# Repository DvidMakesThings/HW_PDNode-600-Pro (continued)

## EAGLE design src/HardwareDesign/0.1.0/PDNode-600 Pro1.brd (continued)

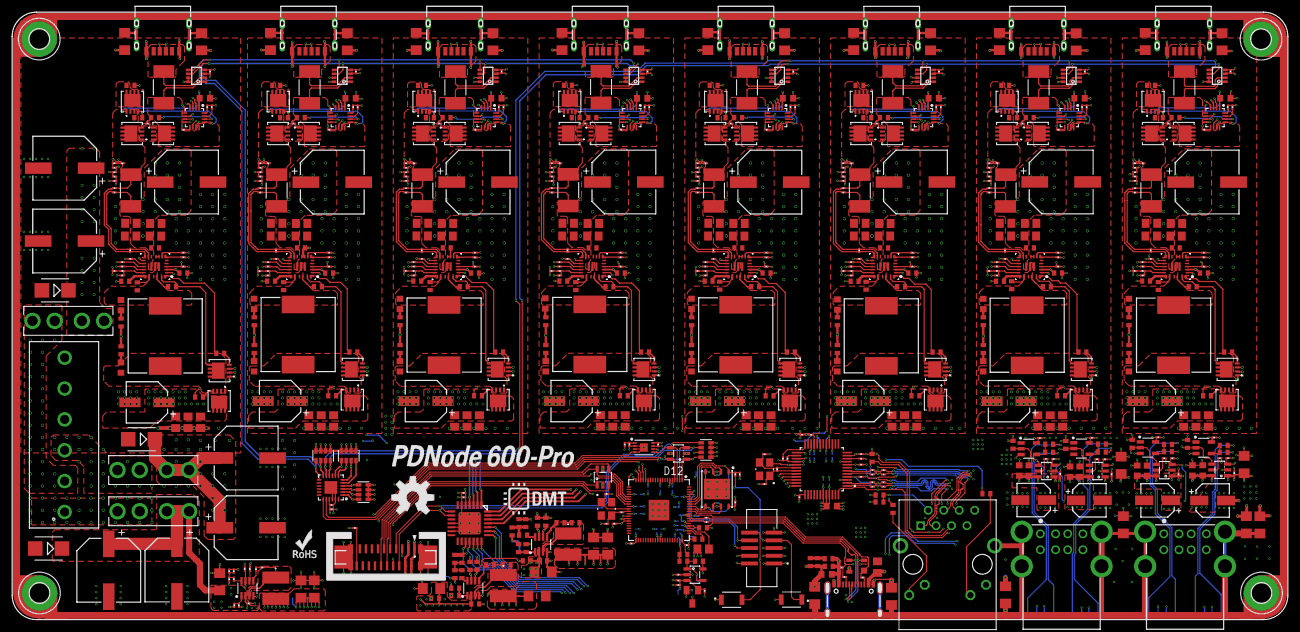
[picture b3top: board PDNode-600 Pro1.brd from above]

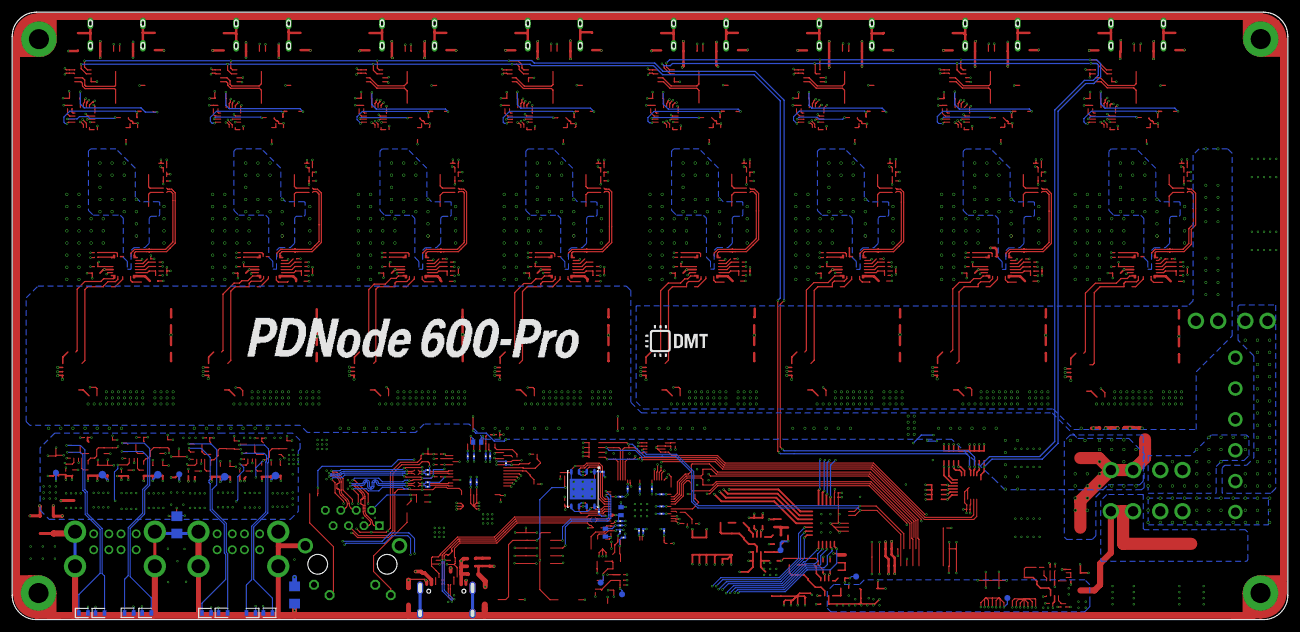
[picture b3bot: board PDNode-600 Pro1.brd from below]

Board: 6 copper layers, 210.0 x 100.0 mm, 755 parts (53 on the bottom side), 468 nets.

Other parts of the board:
U$1: DNI; ROHS_LOGO_0.18_IN
U$2: DNI; OSHW-LOGO-L
U$3, U$4: DMT

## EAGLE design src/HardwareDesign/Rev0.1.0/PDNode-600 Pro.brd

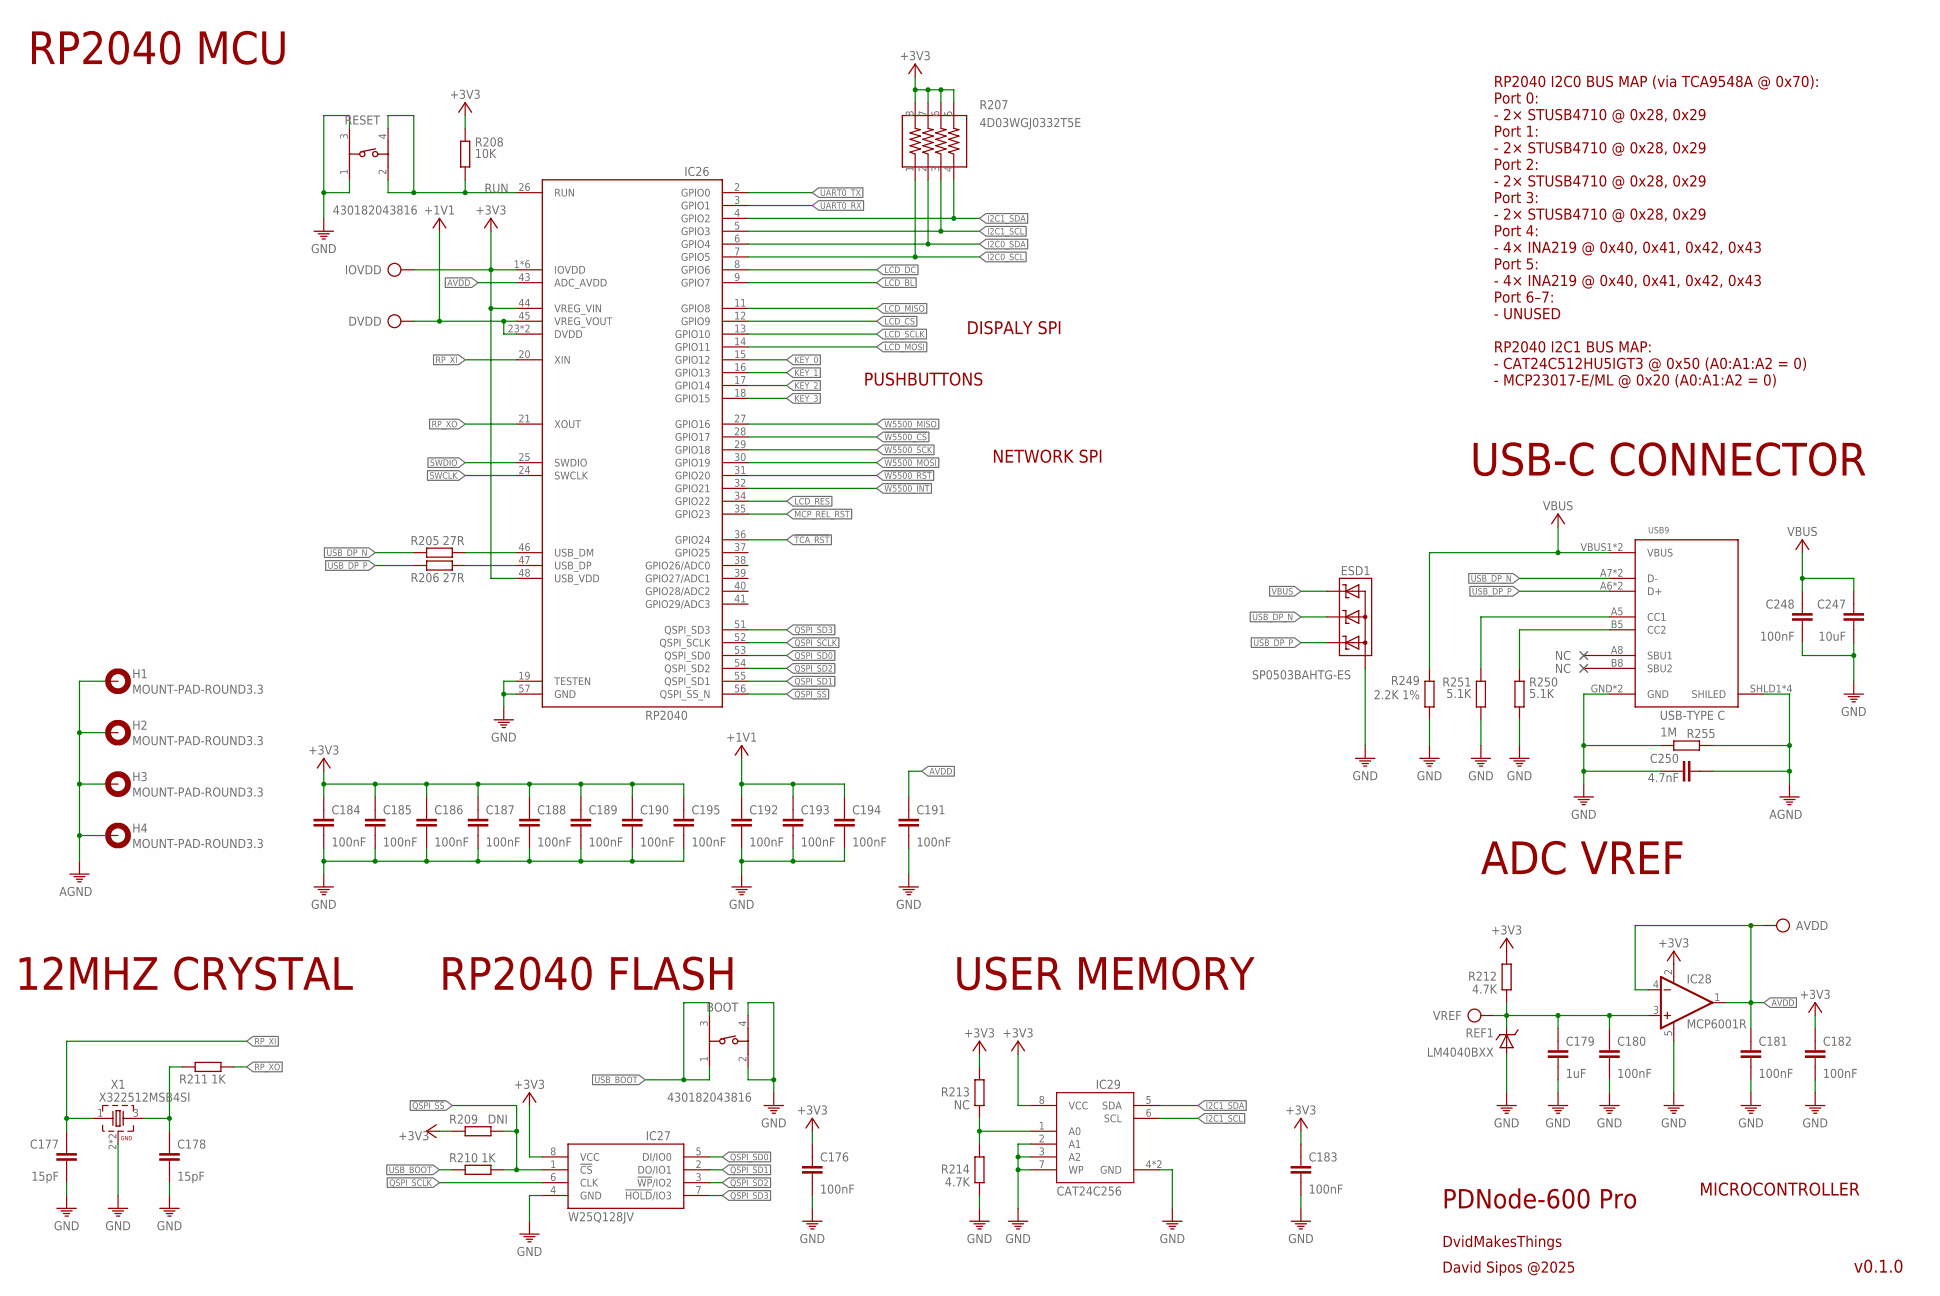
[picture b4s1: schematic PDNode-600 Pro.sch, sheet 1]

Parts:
AVDD: TP
BOOT: 430182043816; 430182050816
C176, C180, C181, C182, C183, C184, C185, C186, C187, C188, C189, C190, C191, C192, C193, C194, C195: 100nF; 0201
C177, C178: 15pF; 0201
C179: 1uF; C0402
C247: 10uF; 0805
C248: 100nF; 0402
C250: 4.7nF; C0402
DVDD: TP
ESD1: SP0503BAHTG-ES; SOT143
H1, H2, H3, H4: MOUNT-PAD-ROUND3.3; 3,3-PAD
IC26: RP2040; QFN40P700X700X100-57T510
IC27: W25Q128JVPIQ; SON127P600X500X75-8N
IC28: MCP6001R; SOT23-5
IC29: CAT24C512HU5IGT3; SON50P300X200X50-9T130X140N
IOVDD: TP
R205, R206: 27R; R0201
R207: 4D03WGJ0332T5E; 742C083103JP
R208: 10K; R0201
R209: DNI; R0201
R210, R211: 1K; R0201
R212: 4.7K; 0402
R213: NC; R0201
R214: 4.7K; R0201
R249: 2.2K 1%; R0201
R250, R251: 5.1K; R0201
R255: 1M; 0402
REF1: LM4040BXX; SOT23
RESET: 430182043816; 430182050816
USB9: USB_C-THT; USB-C
VREF: TP
X1: X322512MSB4SI; WE-XTAL_CFPX-180

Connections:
!QSPI_SS: IC26.56 (QSPI_SS_N), IC27.1 (!CS), R209.1, R210.2
!TCA_RST: IC26.36 (GPIO24); also elsewhere on the board
!W5500_CS: IC26.28 (GPIO17); also elsewhere on the board
!W5500_INT: IC26.32 (GPIO21); also elsewhere on the board
!W5500_RST: IC26.31 (GPIO20); also elsewhere on the board
+1V1: C192.1, C193.1, C194.1, DVDD.TP, IC26.23 (DVDD), IC26.45 (VREG_VOUT), IC26.50 (DVDD)
+3V3: C176.1, C182.1, C183.1, C184.1, C185.1, C186.1, C187.1, C188.1, C189.1, C190.1, C195.1, IC26.1 (IOVDD), IC26.10 (IOVDD), IC26.22 (IOVDD), IC26.33 (IOVDD), IC26.42 (IOVDD), IC26.44 (VREG_VIN), IC26.48 (USB_VDD), IC26.49 (IOVDD), IC27.8 (VCC), IC28.2 (V+), IC29.8 (VCC), IOVDD.TP, R207.5, R207.6, R207.7, R207.8, R208.1, R209.2, R212.2, R213.2; also elsewhere on the board
AGND: C250.1, H1.B3,3, H2.B3,3, H3.B3,3, H4.B3,3, R255.1, USB9.SHLD1 (SHILED), USB9.SHLD2 (SHILED), USB9.SHLD3 (SHILED), USB9.SHLD4 (SHILED); also elsewhere on the board
AVDD: AVDD.TP, C181.1, C191.1, IC26.43 (ADC_AVDD), IC28.1 (OUT), IC28.4 (-IN)
CC1: R251.1, USB9.A5 (CC1)
CC2: R250.1, USB9.B5 (CC2)
GND: BOOT.2, BOOT.4, C176.2, C177.2, C178.2, C179.2, C180.2, C181.2, C182.2, C183.2, C184.2, C185.2, C186.2, C187.2, C188.2, C189.2, C190.2, C191.2, C192.2, C193.2, C194.2, C195.2, C247.2, C248.2, C250.2, ESD1.1 (A), IC26.19 (TESTEN), IC26.57 (GND), IC27.4 (GND), IC28.5 (V-), IC29.2 (A1), IC29.3 (A2), IC29.4 (GND), IC29.7 (WP), IC29.9 (GND), R214.1, R249.2, R250.2, R251.2, R255.2, REF1.2 (A), REF1.3 (A), RESET.1, RESET.3, USB9.GND, USB9.GND2 (GND), X1.2 (GND), X1.4 (GND); also elsewhere on the board
I2C0_SCL: IC26.7 (GPIO5), R207.1; also elsewhere on the board
I2C0_SDA: IC26.6 (GPIO4), R207.2; also elsewhere on the board
I2C1_SCL: IC26.5 (GPIO3), IC29.6 (SCL), R207.3; also elsewhere on the board
I2C1_SDA: IC26.4 (GPIO2), IC29.5 (SDA), R207.4; also elsewhere on the board
KEY_0: IC26.15 (GPIO12); also elsewhere on the board
KEY_1: IC26.16 (GPIO13); also elsewhere on the board
KEY_2: IC26.17 (GPIO14); also elsewhere on the board
KEY_3: IC26.18 (GPIO15); also elsewhere on the board
LCD_BL: IC26.9 (GPIO7); also elsewhere on the board
LCD_CS: IC26.12 (GPIO9); also elsewhere on the board
LCD_DC: IC26.8 (GPIO6); also elsewhere on the board
LCD_MISO: IC26.11 (GPIO8); also elsewhere on the board
LCD_MOSI: IC26.14 (GPIO11); also elsewhere on the board
LCD_RES: IC26.34 (GPIO22); also elsewhere on the board
LCD_SCLK: IC26.13 (GPIO10); also elsewhere on the board
MCP_REL_RST: IC26.35 (GPIO23); also elsewhere on the board
MCU_DP_N: IC26.46 (USB_DM), R205.2
MCU_DP_P: IC26.47 (USB_DP), R206.2
unnamed: C178.1, R211.1, X1.3 (2)
unnamed: IC29.1 (A0), R213.1, R214.2
QSPI_SCLK: IC26.52 (QSPI_SCLK), IC27.6 (CLK)
QSPI_SD0: IC26.53 (QSPI_SD0), IC27.5 (DI/IO0)
QSPI_SD1: IC26.55 (QSPI_SD1), IC27.2 (DO/IO1)
QSPI_SD2: IC26.54 (QSPI_SD2), IC27.3 (!WP!/IO2)
QSPI_SD3: IC26.51 (QSPI_SD3), IC27.7 (!HOLD!/IO3)
RP_XI: C177.1, IC26.20 (XIN), X1.1
RP_XO: IC26.21 (XOUT), R211.2
RUN: IC26.26 (RUN), R208.2, RESET.2, RESET.4
SWCLK: IC26.24 (SWCLK)
SWDIO: IC26.25 (SWDIO)
UART0_RX: IC26.3 (GPIO1)
UART0_TX: IC26.2 (GPIO0)
USB_BOOT: BOOT.1, BOOT.3, R210.1
USB_DP_N: ESD1.3 (C2), R205.1, USB9.A7 (D-), USB9.B7 (D-)
USB_DP_P: ESD1.2 (C1), R206.1, USB9.A6 (D+), USB9.B6 (D+)
VBUS: C247.1, C248.1, ESD1.4 (C3), R249.1, USB9.VBUS1 (VBUS), USB9.VBUS2 (VBUS)
VREF: C179.1, C180.1, IC28.3 (+IN), R212.1, REF1.1 (C), VREF.TP
W5500_MISO: IC26.27 (GPIO16); also elsewhere on the board
W5500_MOSI: IC26.30 (GPIO19); also elsewhere on the board
W5500_SCK: IC26.29 (GPIO18); also elsewhere on the board

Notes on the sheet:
PDNode-600 Pro
DvidMakesThings
David Sipos @2025
RP2040 MCU
RP2040 FLASH
12MHZ CRYSTAL
USER MEMORY
ADC VREF
RP2040 I2C0 BUS MAP (via TCA9548A @ 0x70): Port 0: - 2× STUSB4710 @ 0x28, 0x29 Port 1: - 2× STUSB4710 @ 0x28, 0x29 Port 2: - 2× STUSB4710 @ 0x28, 0x29 Port 3: - 2× STUSB4710 @ 0x28, 0x29 Port 4: - 4× INA219 @ 0x40, 0x41, 0x42, 0x43 Port 5: - 4× INA219 @ 0x40, 0x41, 0x42, 0x43 Port 6–7: - UNUSED RP2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
USB-C CONNECTOR
NETWORK SPI
DISPALY SPI
PUSHBUTTONS
MICROCONTROLLER
v0.1.0

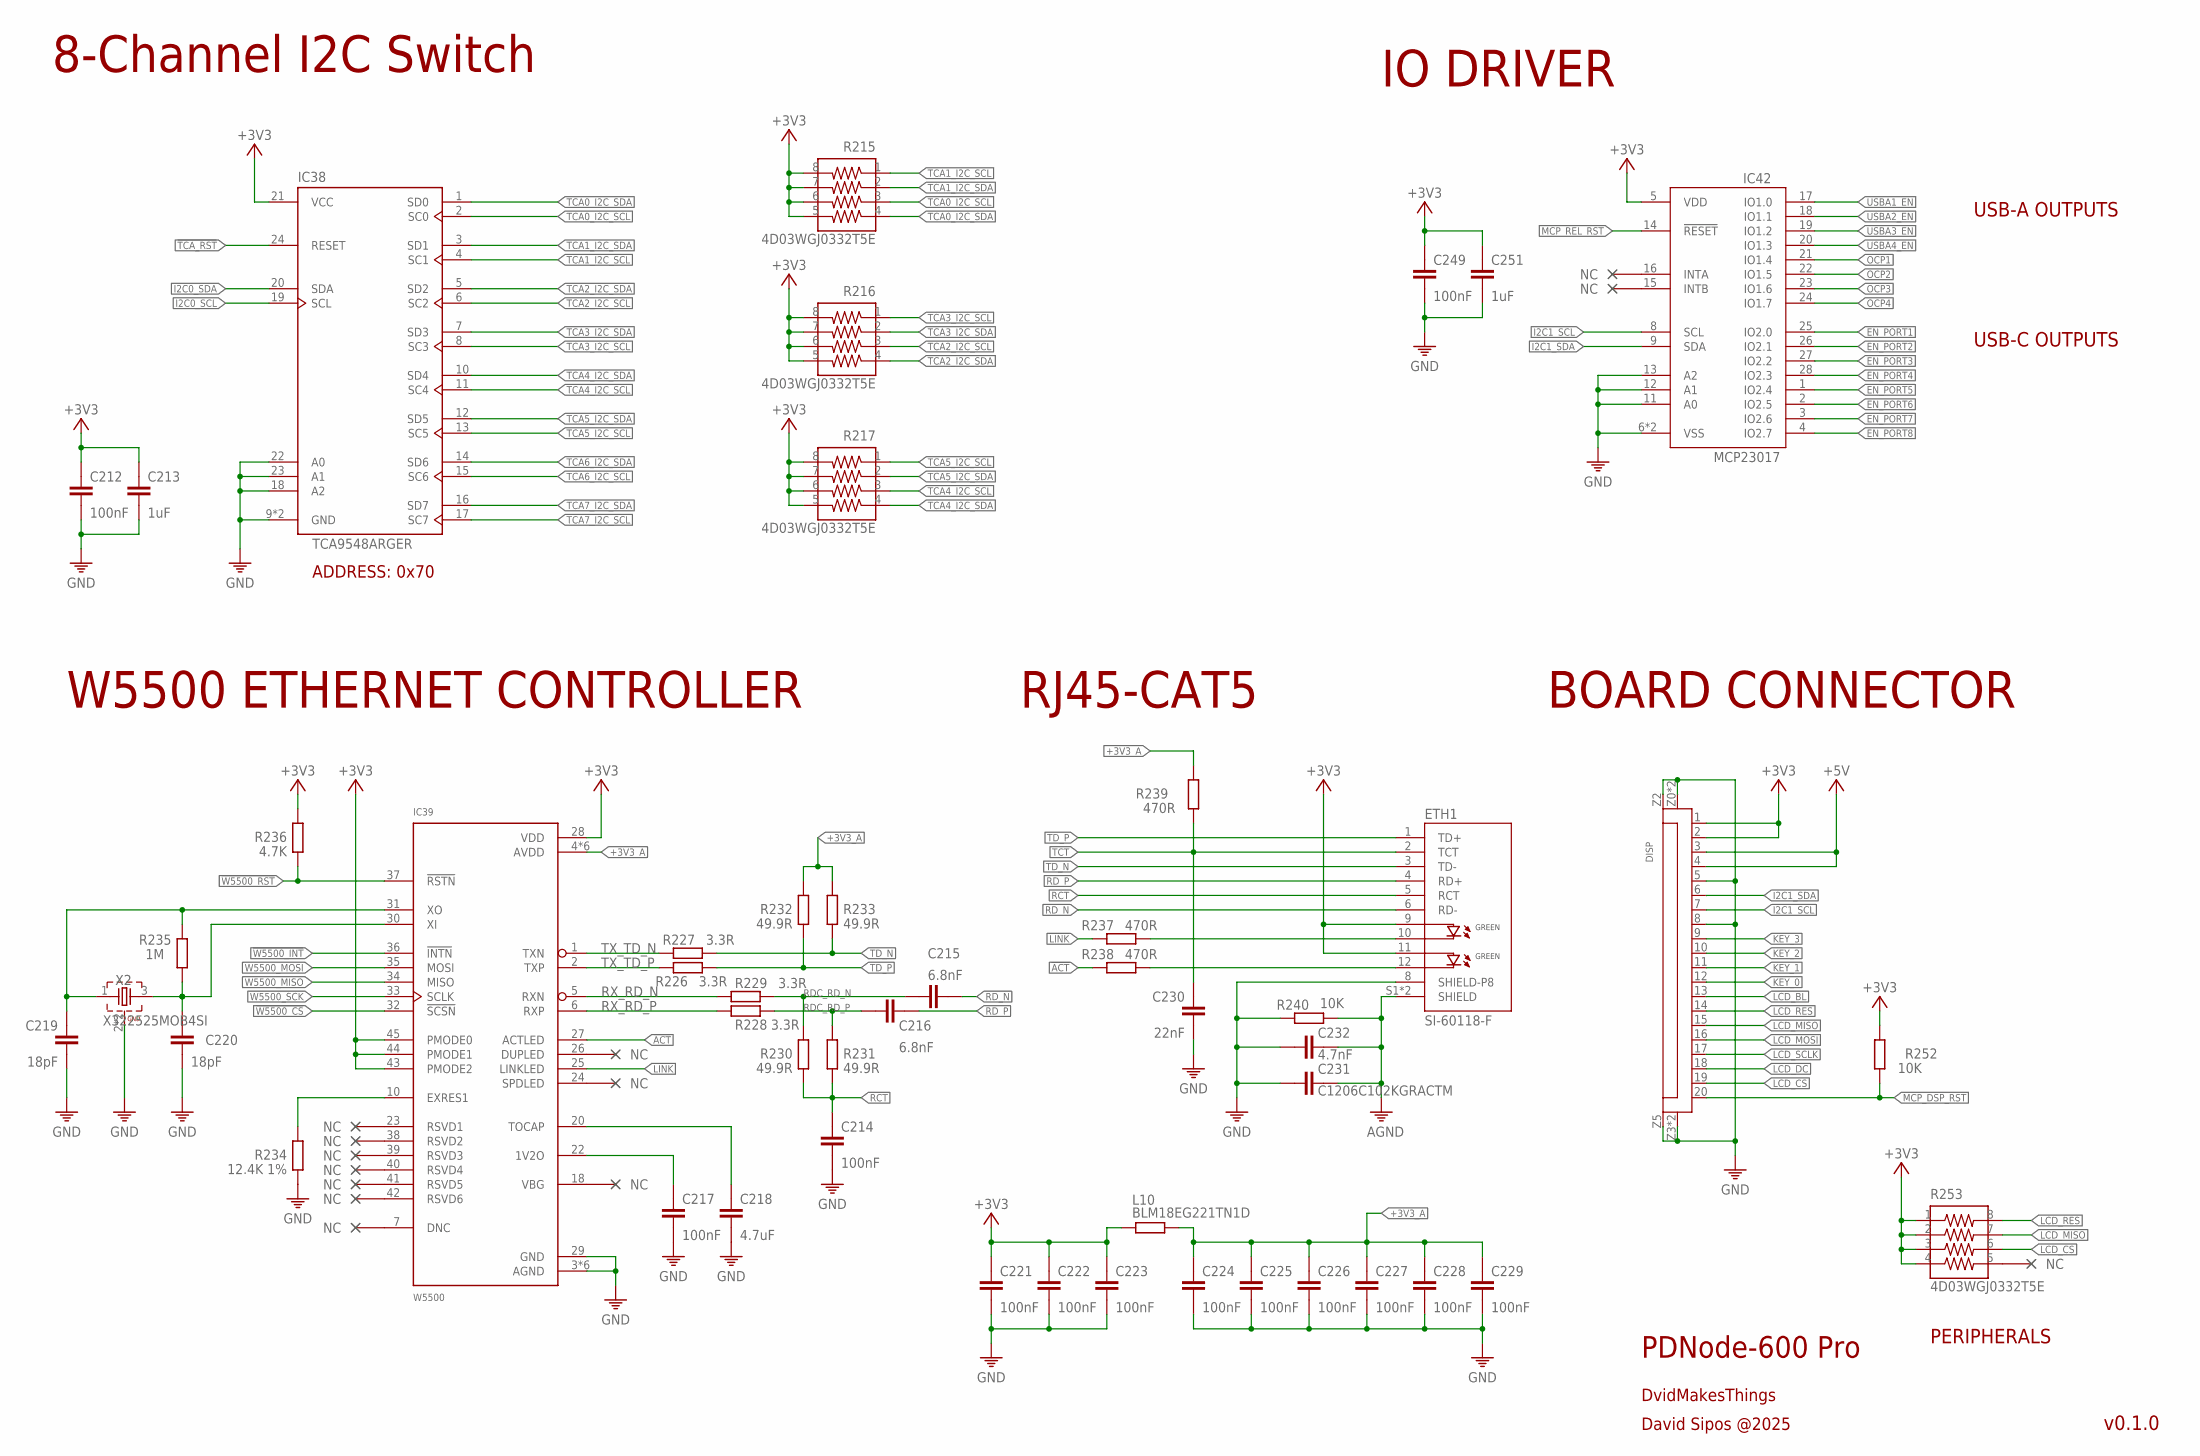
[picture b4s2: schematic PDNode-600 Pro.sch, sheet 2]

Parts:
C212, C214, C217, C221, C222, C223, C224, C225, C226, C227, C228, C229, C249: 100nF; 0201
C213, C251: 1uF; 0201
C215, C216: 6.8nF; 0201
C218: 4.7uF; C0402
C219, C220: 18pF; 0201
C230: 22nF; C0402
C231: C1206C102KGRACTM; C1206
C232: 4.7nF; C0402
DISP: AFC11-S20ICC-00; FPC20
ETH1: SI-60118-F; RJ45-CAT5
IC38: TCA9548ARGER; QFN50P400X400X100-25T210N
IC39: W5500; LQFP48
IC42: MCP23017-E/ML; QFN28[6X6]ML
L10: BLM18EG221TN1D; 0603
R215, R216, R217: 4D03WGJ0332T5E; YC164-JR-0733RL
R226, R227, R228, R229: 3.3R; R0201
R230, R231, R232, R233: 49.9R; R0201
R234: 12.4K 1%; R0201
R235: 1M; R0201
R236: 4.7K; R0201
R237, R238, R239: 470R; 0402
R240, R252: 10K; 0402
R253: 4D03WGJ0332T5E; 742C083103JP
X2: X322525MOB4SI; WE-XTAL_CFPX-180

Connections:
!ACT: IC39.27 (ACTLED), R238.1
!LINK: IC39.25 (LINKLED), R237.1
!TCA_RST: IC38.24 (RESET); also elsewhere on the board
!W5500_CS: IC39.32 (!SCSN); also elsewhere on the board
!W5500_INT: IC39.36 (!INTN); also elsewhere on the board
!W5500_RST: IC39.37 (!RSTN), R236.1; also elsewhere on the board
+3V3: C212.1, C213.1, C221.1, C222.1, C223.1, C249.1, C251.1, DISP.1, DISP.2, ETH1.9 (GA1), ETH1.11 (GA2), IC38.21 (VCC), IC39.28 (VDD), IC39.43 (PMODE2), IC39.44 (PMODE1), IC39.45 (PMODE0), IC42.5 (VDD), L10.1, R215.5, R215.6, R215.7, R215.8, R216.5, R216.6, R216.7, R216.8, R217.5, R217.6, R217.7, R217.8, R236.2, R252.2, R253.1, R253.2, R253.3, R253.4; also elsewhere on the board
+3V3_A: C224.1, C225.1, C226.1, C227.1, C228.1, C229.1, IC39.4 (AVDD), IC39.8 (AVDD), IC39.11 (AVDD), IC39.15 (AVDD), IC39.17 (AVDD), IC39.21 (AVDD), L10.2, R232.2, R233.2, R239.2
+5V: DISP.3, DISP.4
AGND: C231.2, C232.2, ETH1.S1 (SHIELD), ETH1.S2 (SHIELD), R240.2; also elsewhere on the board
EN_PORT1: IC42.25 (IO2.0); also elsewhere on the board
EN_PORT2: IC42.26 (IO2.1); also elsewhere on the board
EN_PORT3: IC42.27 (IO2.2); also elsewhere on the board
EN_PORT4: IC42.28 (IO2.3); also elsewhere on the board
EN_PORT5: IC42.1 (IO2.4); also elsewhere on the board
EN_PORT6: IC42.2 (IO2.5); also elsewhere on the board
EN_PORT7: IC42.3 (IO2.6); also elsewhere on the board
EN_PORT8: IC42.4 (IO2.7); also elsewhere on the board
GND: C212.2, C213.2, C214.2, C217.2, C218.2, C219.2, C220.2, C221.2, C222.2, C223.2, C224.2, C225.2, C226.2, C227.2, C228.2, C229.2, C230.2, C231.1, C232.1, C249.2, C251.2, DISP.5, DISP.8, DISP.Z0 (Z1), DISP.Z1, DISP.Z2, DISP.Z3, DISP.Z4 (Z3), DISP.Z5 (Z4), ETH1.8 (SHIELD-P8), IC38.9 (GND), IC38.18 (A2), IC38.22 (A0), IC38.23 (A1), IC38.25 (GND), IC39.3 (AGND), IC39.9 (AGND), IC39.14 (AGND), IC39.16 (AGND), IC39.19 (AGND), IC39.29 (GND), IC39.48 (AGND), IC42.6 (VSS), IC42.11 (A0), IC42.12 (A1), IC42.13 (A2), IC42.PAD (VSS), R234.1, R240.1, X2.2 (GND), X2.4 (GND); also elsewhere on the board
I2C0_SCL: IC38.19 (SCL); also elsewhere on the board
I2C0_SDA: IC38.20 (SDA); also elsewhere on the board
I2C1_SCL: DISP.7, IC42.8 (SCL); also elsewhere on the board
I2C1_SDA: DISP.6, IC42.9 (SDA); also elsewhere on the board
KEY_0: DISP.12; also elsewhere on the board
KEY_1: DISP.11; also elsewhere on the board
KEY_2: DISP.10; also elsewhere on the board
KEY_3: DISP.9; also elsewhere on the board
LCD_BL: DISP.13; also elsewhere on the board
LCD_CS: DISP.19, R253.6; also elsewhere on the board
LCD_DC: DISP.18; also elsewhere on the board
LCD_MISO: DISP.15, R253.7; also elsewhere on the board
LCD_MOSI: DISP.16; also elsewhere on the board
LCD_RES: DISP.14, R253.8; also elsewhere on the board
LCD_SCLK: DISP.17; also elsewhere on the board
MCP_DSP_RST: DISP.20, R252.1
MCP_REL_RST: IC42.14 (!RESET); also elsewhere on the board
unnamed: IC39.10 (EXRES1), R234.2
unnamed: C217.1, IC39.22 (1V2O)
unnamed: C218.1, IC39.20 (TOCAP)
unnamed: C220.1, IC39.30 (XI), R235.1, X2.3 (2)
unnamed: ETH1.10 (GK1), R237.2
unnamed: ETH1.12 (GK2), R238.2
OCP1: IC42.21 (IO1.4); also elsewhere on the board
OCP2: IC42.22 (IO1.5); also elsewhere on the board
OCP3: IC42.23 (IO1.6); also elsewhere on the board
OCP4: IC42.24 (IO1.7); also elsewhere on the board
RCT: C214.1, ETH1.5 (RCT), R230.1, R231.1
RDC_RD_N: C215.1, R229.2, R230.2
RDC_RD_P: C216.1, R228.2, R231.2
RD_N: C215.2, ETH1.6 (RD-)
RD_P: C216.2, ETH1.4 (RD+)
RX_RD_N: IC39.5 (RXN), R229.1
RX_RD_P: IC39.6 (RXP), R228.1
TCA0_I2C_SCL: IC38.2 (SC0), R215.3; also elsewhere on the board
TCA0_I2C_SDA: IC38.1 (SD0), R215.4; also elsewhere on the board
TCA1_I2C_SCL: IC38.4 (SC1), R215.1; also elsewhere on the board
TCA1_I2C_SDA: IC38.3 (SD1), R215.2; also elsewhere on the board
TCA2_I2C_SCL: IC38.6 (SC2), R216.3; also elsewhere on the board
TCA2_I2C_SDA: IC38.5 (SD2), R216.4; also elsewhere on the board
TCA3_I2C_SCL: IC38.8 (SC3), R216.1; also elsewhere on the board
TCA3_I2C_SDA: IC38.7 (SD3), R216.2; also elsewhere on the board
TCA4_I2C_SCL: IC38.11 (SC4), R217.3; also elsewhere on the board
TCA4_I2C_SDA: IC38.10 (SD4), R217.4; also elsewhere on the board
TCA5_I2C_SCL: IC38.13 (SC5), R217.1; also elsewhere on the board
TCA5_I2C_SDA: IC38.12 (SD5), R217.2; also elsewhere on the board
TCA6_I2C_SCL: IC38.15 (SC6)
TCA6_I2C_SDA: IC38.14 (SD6)
TCA7_I2C_SCL: IC38.17 (SC7)
TCA7_I2C_SDA: IC38.16 (SD7)
TCT: C230.1, ETH1.2 (TCT), R239.1
TD_N: ETH1.3 (TD-), R227.2, R233.1
TD_P: ETH1.1 (TD+), R226.2, R232.1
TX_TD_N: IC39.1 (TXN), R227.1
TX_TD_P: IC39.2 (TXP), R226.1
USBA1_EN: IC42.17 (IO1.0); also elsewhere on the board
USBA2_EN: IC42.18 (IO1.1); also elsewhere on the board
USBA3_EN: IC42.19 (IO1.2); also elsewhere on the board
USBA4_EN: IC42.20 (IO1.3); also elsewhere on the board
W5500_MISO: IC39.34 (MISO); also elsewhere on the board
W5500_MOSI: IC39.35 (MOSI); also elsewhere on the board
W5500_SCK: IC39.33 (SCLK); also elsewhere on the board
XO: C219.1, IC39.31 (XO), R235.2, X2.1

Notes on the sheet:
PDNode-600 Pro
DvidMakesThings
David Sipos @2025
8-Channel I2C Switch
ADDRESS: 0x70
W5500 ETHERNET CONTROLLER
RJ45-CAT5
IO DRIVER
USB-A OUTPUTS
USB-C OUTPUTS
BOARD CONNECTOR
PERIPHERALS
v0.1.0

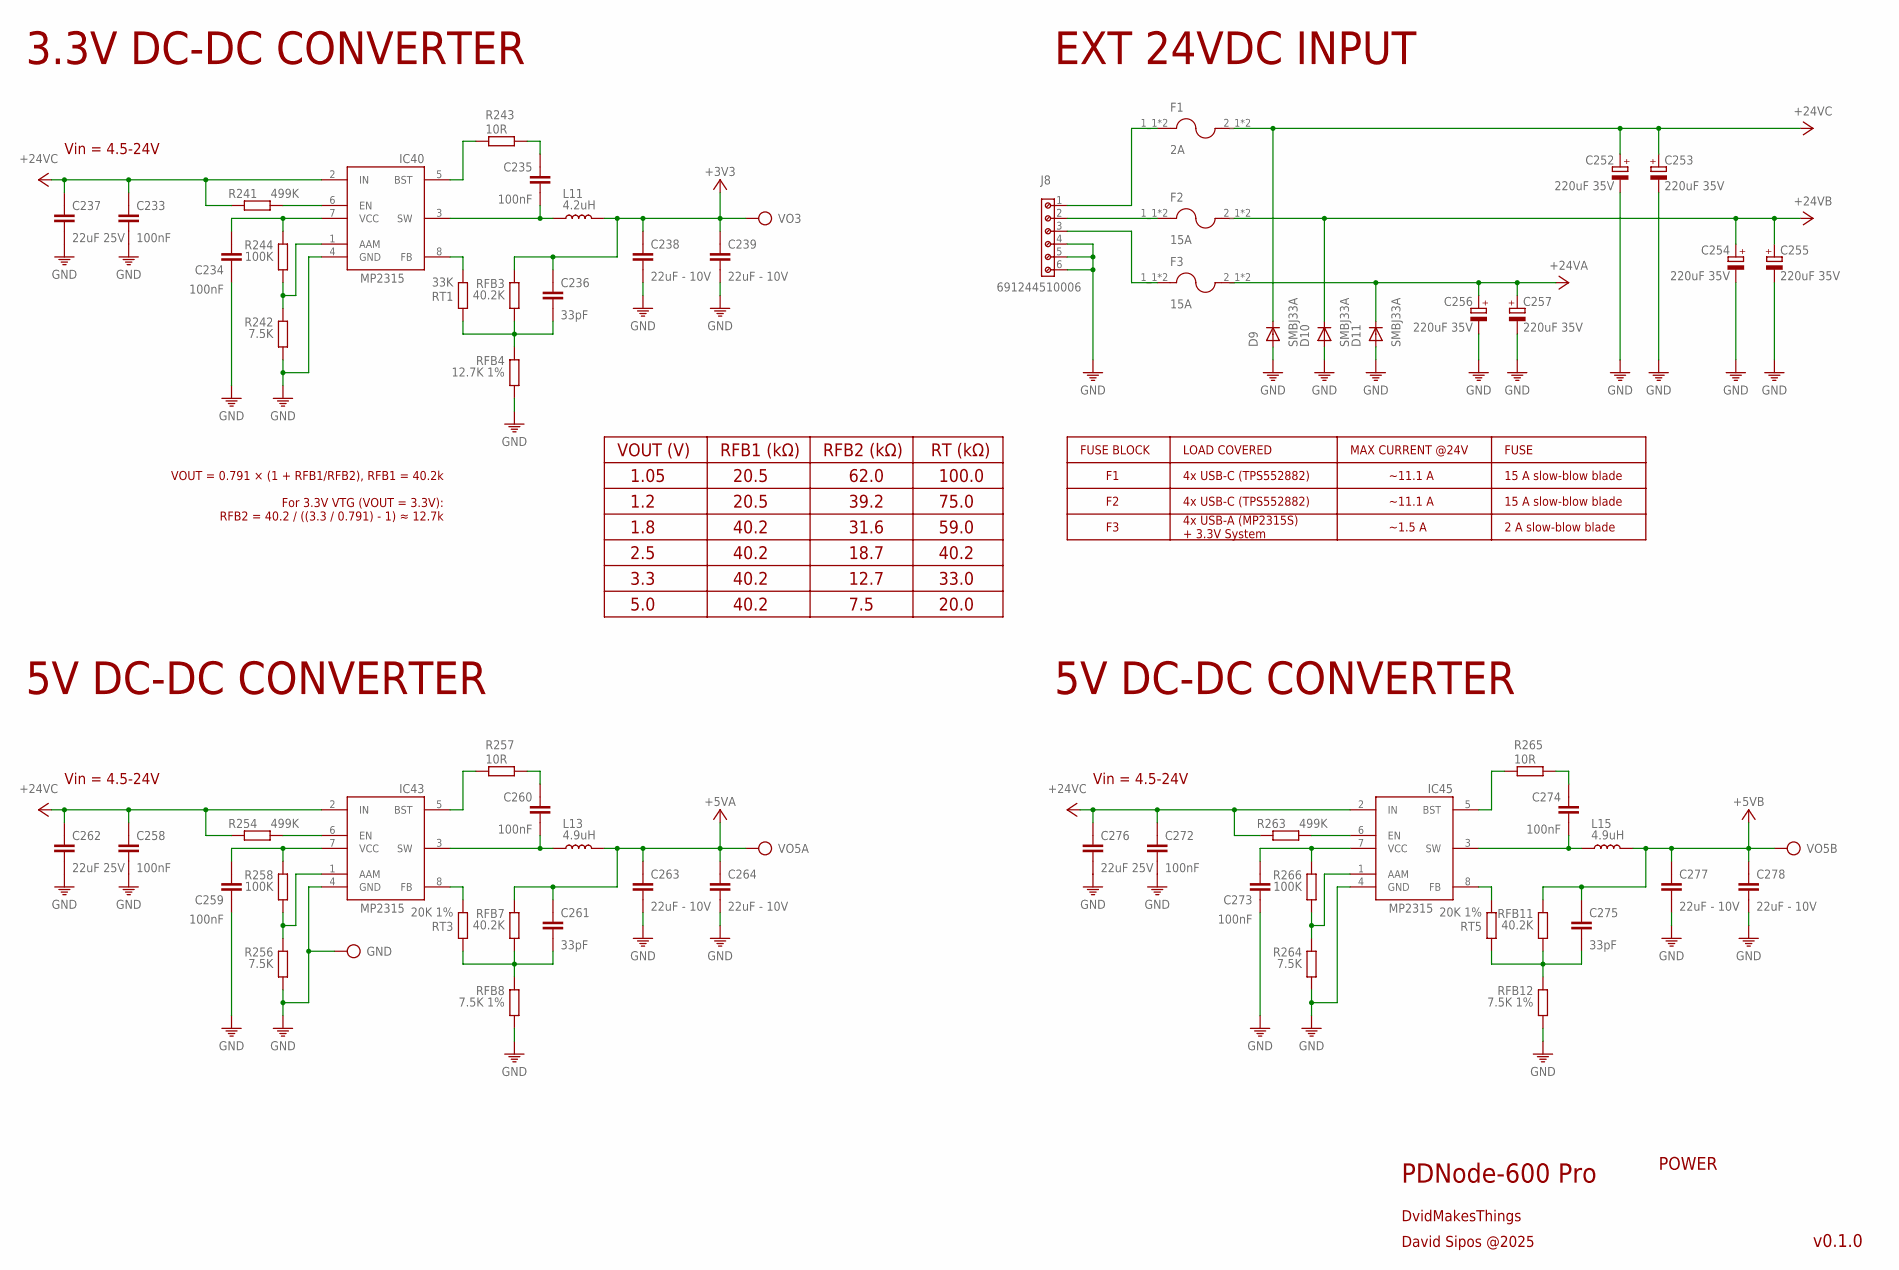
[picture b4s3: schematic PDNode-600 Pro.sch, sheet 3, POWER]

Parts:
C233, C234, C235, C258, C259, C260, C272, C273, C274: 100nF; 0201
C236, C261, C275: 33pF; 0201
C237, C262, C276: 22uF 25V; C1206
C238, C239, C263, C264, C277, C278: 22uF - 10V; C1206
C252, C253, C254, C255, C256, C257: 220uF 35V; CAPAE830X1050N
D9, D10, D11: SMBJ33A; SMB
F1: 2A; FUSE_3544-2
F2, F3: 15A; FUSE_3544-2
GND: TP
IC40, IC43, IC45: MP2315S; SOT65P280X110-8N
J8: 691244510006
L11: 4.2uH; SRR5228A
L13, L15: 4.9uH; SRR5228A
R241, R254, R263: 499K; R0201
R242, R256, R264: 7.5K; R0201
R243, R257, R265: 10R; R0201
R244, R258, R266: 100K; R0201
RFB3, RFB7, RFB11: 40.2K; R0201
RFB4: 12.7K 1%; R0201
RFB8, RFB12: 7.5K 1%; R0201
RT1: 33K; R0201
RT3, RT5: 20K 1%; R0201
VO3, VO5A, VO5B: TP

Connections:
3V3_EN_SYS1: IC40.6 (EN), R241.2
3V3_EN_SYS3: IC43.6 (EN), R254.2
3V3_EN_SYS5: IC45.6 (EN), R263.2
24VINA: F2.1_1 (1), F2.1_2 (1), J8.2
24VINB: F3.1_1 (1), F3.1_2 (1), J8.3
24VINC: F1.1_1 (1), F1.1_2 (1), J8.1
+3V3: C236.1, C238.1, C239.1, L11.2, RFB3.1, VO3.TP; also elsewhere on the board
+5VA: C261.1, C263.1, C264.1, L13.2, RFB7.1, VO5A.TP; also elsewhere on the board
+5VB: C275.1, C277.1, C278.1, L15.2, RFB11.1, VO5B.TP; also elsewhere on the board
+24V_A: C256.1 (+), C257.1 (+), D11.C, F3.2_1 (2), F3.2_2 (2); also elsewhere on the board
+24V_B: C254.1 (+), C255.1 (+), D10.C, F2.2_1 (2), F2.2_2 (2); also elsewhere on the board
+24V_C: C233.1, C237.1, C252.1 (+), C253.1 (+), C258.1, C262.1, C272.1, C276.1, D9.C, F1.2_1 (2), F1.2_2 (2), IC40.2 (IN), IC43.2 (IN), IC45.2 (IN), R241.1, R254.1, R263.1
GND: C233.2, C234.2, C237.2, C238.2, C239.2, C252.2 (-), C253.2 (-), C254.2 (-), C255.2 (-), C256.2 (-), C257.2 (-), C258.2, C259.2, C262.2, C263.2, C264.2, C272.2, C273.2, C276.2, C277.2, C278.2, D9.A, D10.A, D11.A, GND.TP, IC40.4 (GND), IC43.4 (GND), IC45.4 (GND), J8.4, J8.5, J8.6, R242.2, R256.2, R264.2, RFB4.2, RFB8.2, RFB12.2; also elsewhere on the board
unnamed: IC40.5 (BST), R243.2
unnamed: IC40.8 (FB), RT1.1
unnamed: C235.2, IC40.3 (SW), L11.1
unnamed: C235.1, R243.1
unnamed: C236.2, RFB3.2, RFB4.1, RT1.2
unnamed: C234.1, IC40.7 (VCC), R244.1
unnamed: IC40.1 (AAM), R242.1, R244.2
unnamed: IC43.5 (BST), R257.2
unnamed: IC43.8 (FB), RT3.1
unnamed: C260.2, IC43.3 (SW), L13.1
unnamed: C260.1, R257.1
unnamed: C261.2, RFB7.2, RFB8.1, RT3.2
unnamed: C259.1, IC43.7 (VCC), R258.1
unnamed: IC43.1 (AAM), R256.1, R258.2
unnamed: IC45.5 (BST), R265.2
unnamed: IC45.8 (FB), RT5.1
unnamed: C274.2, IC45.3 (SW), L15.1
unnamed: C274.1, R265.1
unnamed: C275.2, RFB11.2, RFB12.1, RT5.2
unnamed: C273.1, IC45.7 (VCC), R266.1
unnamed: IC45.1 (AAM), R264.1, R266.2

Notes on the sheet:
PDNode-600 Pro
DvidMakesThings
David Sipos @2025
VOUT = 0.791 × (1 + RFB1/RFB2), RFB1 = 40.2k For 3.3V VTG (VOUT = 3.3V): RFB2 = 40.2 / ((3.3 / 0.791) - 1) ≈ 12.7k
VOUT (V)
EXT 24VDC INPUT
FUSE BLOCK
LOAD COVERED
MAX CURRENT @24V
FUSE
4x USB-C (TPS552882)
4x USB-A (MP2315S) + 3.3V System
~11.1 A
~1.5 A
15 A slow-blow blade
2 A slow-blow blade
RFB1 (kΩ)
RFB2 (kΩ)
RT (kΩ)
1.05
1.2
1.8
3.3
5.0
20.5
40.2
62.0
39.2
31.6
18.7
12.7
7.5
2.5
100.0
75.0
59.0
33.0
20.0
POWER
v0.1.0

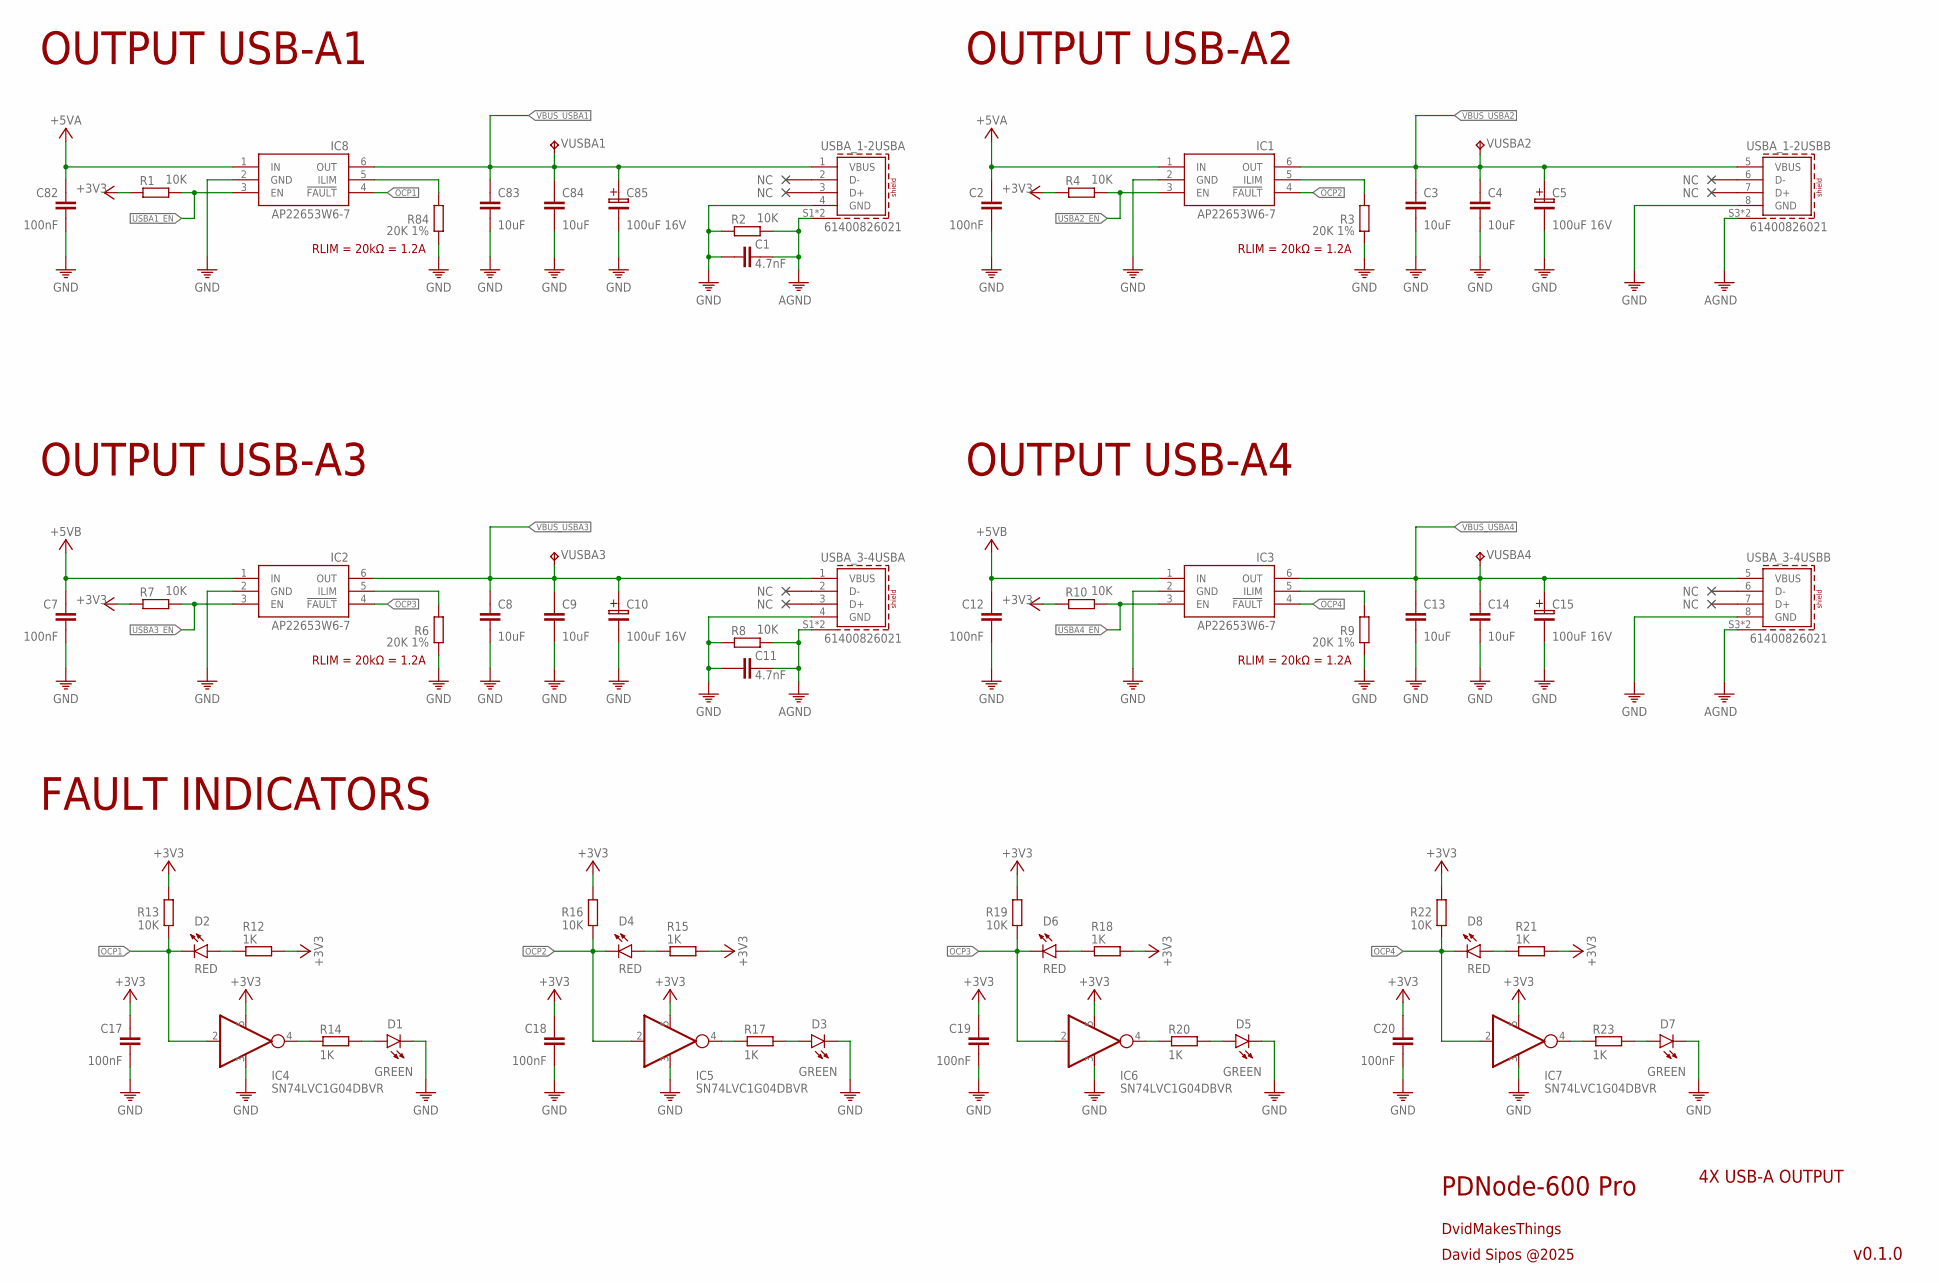
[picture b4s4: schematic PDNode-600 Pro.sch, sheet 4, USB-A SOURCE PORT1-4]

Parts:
C1, C11: 4.7nF; C0402
C2, C7, C12, C17, C18, C19, C20, C82: 100nF; C0402
C3, C4, C8, C9, C13, C14, C83, C84: 10uF; C0805
C5, C10, C15, C85: 100uF 16V; 100UF-16V
D1, D3, D5, D7: GREEN; LEDC1608X35N_FLAT-G
D2, D4, D6, D8: RED; LEDC1608X35N_FLAT-R
IC1, IC2, IC3, IC8: AP22653W6-7; SOT23-6
IC4, IC5, IC6, IC7: SN74LVC1G04DBVR; SOT95P280X145-5N
R1, R2, R4, R7, R8, R10, R13, R16, R19, R22: 10K; 0402
R3, R6, R9, R84: 20K 1%; 0402
R12, R14, R15, R17, R18, R20, R21, R23: 1K; 0402
USBA_1-2, USBA_3-4: 61400826021
VUSBA1, VUSBA2, VUSBA3, VUSBA4: TPB1,27; B1,27

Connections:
+3V3: C17.1, C18.1, C19.1, C20.1, IC4.5 (V+), IC5.5 (V+), IC6.5 (V+), IC7.5 (V+), R1.1, R4.1, R7.1, R10.1, R12.2, R13.2, R15.2, R16.2, R18.2, R19.2, R21.2, R22.2; also elsewhere on the board
+5VA: C2.1, C82.1, IC1.1 (IN), IC8.1 (IN); also elsewhere on the board
+5VB: C7.1, C12.1, IC2.1 (IN), IC3.1 (IN); also elsewhere on the board
AGND: C1.2, C11.2, R2.2, R8.2, USBA_1-2.S1 (SHIELD), USBA_1-2.S2 (SHIELD), USBA_1-2.S3 (SHIELD), USBA_1-2.S4 (SHIELD), USBA_3-4.S1 (SHIELD), USBA_3-4.S2 (SHIELD), USBA_3-4.S3 (SHIELD), USBA_3-4.S4 (SHIELD); also elsewhere on the board
GND: C1.1, C2.2, C3.2, C4.2, C5.2, C7.2, C8.2, C9.2, C10.2, C11.1, C12.2, C13.2, C14.2, C15.2, C17.2, C18.2, C19.2, C20.2, C82.2, C83.2, C84.2, C85.2, D1.C, D3.C, D5.C, D7.C, IC1.2 (GND), IC2.2 (GND), IC3.2 (GND), IC4.3 (V-), IC5.3 (V-), IC6.3 (V-), IC7.3 (V-), IC8.2 (GND), R2.1, R3.2, R6.2, R8.1, R9.2, R84.2, USBA_1-2.4 (GND), USBA_1-2.8 (GND), USBA_3-4.4 (GND), USBA_3-4.8 (GND); also elsewhere on the board
unnamed: IC1.5 (ILIM), R3.1
unnamed: IC2.5 (ILIM), R6.1
unnamed: IC3.5 (ILIM), R9.1
unnamed: D2.A, R12.1
unnamed: IC4.4 (OUT), R14.1
unnamed: D1.A, R14.2
unnamed: D4.A, R15.1
unnamed: IC5.4 (OUT), R17.1
unnamed: D3.A, R17.2
unnamed: D6.A, R18.1
unnamed: IC6.4 (OUT), R20.1
unnamed: D5.A, R20.2
unnamed: D8.A, R21.1
unnamed: IC7.4 (OUT), R23.1
unnamed: D7.A, R23.2
unnamed: IC8.5 (ILIM), R84.1
OCP1: D2.C, IC4.2 (IN), IC8.4 (!FAULT), R13.1; also elsewhere on the board
OCP2: D4.C, IC1.4 (!FAULT), IC5.2 (IN), R16.1; also elsewhere on the board
OCP3: D6.C, IC2.4 (!FAULT), IC6.2 (IN), R19.1; also elsewhere on the board
OCP4: D8.C, IC3.4 (!FAULT), IC7.2 (IN), R22.1; also elsewhere on the board
USBA1_EN: IC8.3 (EN), R1.2; also elsewhere on the board
USBA2_EN: IC1.3 (EN), R4.2; also elsewhere on the board
USBA3_EN: IC2.3 (EN), R7.2; also elsewhere on the board
USBA4_EN: IC3.3 (EN), R10.2; also elsewhere on the board
VBUS_USBA1: C83.1, C84.1, C85.1, IC8.6 (OUT), USBA_1-2.1 (VBUS), VUSBA1.TP
VBUS_USBA2: C3.1, C4.1, C5.1, IC1.6 (OUT), USBA_1-2.5 (VBUS), VUSBA2.TP
VBUS_USBA3: C8.1, C9.1, C10.1, IC2.6 (OUT), USBA_3-4.1 (VBUS), VUSBA3.TP
VBUS_USBA4: C13.1, C14.1, C15.1, IC3.6 (OUT), USBA_3-4.5 (VBUS), VUSBA4.TP

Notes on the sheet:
PDNode-600 Pro
DvidMakesThings
David Sipos @2025
OUTPUT USB-A1
RLIM = 20kΩ = 1.2A
OUTPUT USB-A2
OUTPUT USB-A3
OUTPUT USB-A4
FAULT INDICATORS
4X USB-A OUTPUT
v0.1.0
